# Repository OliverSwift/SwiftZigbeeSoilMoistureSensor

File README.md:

# Swift Zigbee Soil Moisture Sensor

This hardware project is about creating a Zigbee adapter to the existing Capacitive Soil Moisture Sensor 1.2 widely available.

## How to use it

[Here is](doc/Swift%20Zigbee%20Soil%20Moisture%20Sensor.pdf) the small user manual.

It works well with Conbee2 and SONOFF zigbee concentrators used with Home Assistant.

CR2032 coin battery should allow approximately two years of autonomy.

## Technical background

After some trials on STM32WB55 which permanently failed to connect to a zigbee concentrator (Conbee2) I finally chose the nrf52840 SOC from Nordic Semicondudtors. It is very well known in the BLE world and decided to test its Zigbee capabilities and it was successful. Best solutions are provided by Texas Instrument (CC2350) and Silabs (EFR32MG1) at the moment. Using nrf52840 for Zigbee is the challenge here.

The solution is based on ZephyrOS and NRF Connect SDK version 2.6.1 that includes ZBoss proprietary Zigbee stack. One of the challenging aspect of this project is the power consumption. The nrf52840 is able to enter deep sleep and only consumes 2.5µA approximately. Now I had to face that the Capacitive Sensor is based on a NE555. Surprisingly it is not the CMOS version and is supposed to be power supplied between 5 and 15V. But it can be with only 3.3V. Any attempt to power supply below this value resulted in unstable sensor. So I decided to use 3.3V for the whole device (MCU+sensor). This led to choosing a boost converter so a coin battery can be used, ideally CR2032.

The average current measurement is about 10µA, which should allow 2 year autonomy. Probe measurement is done every 30 minutes. When it occurs, the tiny LED lits.

The project was developed thanks to [nRF52840 DK board](doc/nRF52840_DK_User_Guide_v1.2.pdf). I used the OB JLink capability to flash the target board.

The nRF52840 module (E73-2G4M08S1C) comes from EBYTE. It doesn't have the external 32kHz crystal, but this one isn't useful for Zigbee applications.

Documentation folder includes:

- [Electronic schematics](doc/schematics-2.0.pdf)
- Main components datasheet (nrf52840 and tps61097a)
- [How to build and flash](doc/how_to_compile.md)

CAD folder includes:

- [KiCAD](cad/KiCAD) project files
- [FreeCAD](cad/FreeCAD) projet, a desparate attempt to design a [box with a lid](cad/FreeCAD/box+lid.stl).

## Project details

### Building system

The ZephyrOS ecosystem provides high level build system called _west_. It's a pile of Python scripts that doesn't do much else than invoking _cmake_. I quickly realized that cmake can be used solely without the cumbersome _west_ layer. I ended up with a simple Makefile to achieve the bare necessities. 

Forgot to say that I use Linux (Ubuntu or Debian), but this should work well with MacOSX either. I struggled to make Nordic tools to run on Ubuntu 24.04 (app images need to run without sandbox), but this is definitely possible.

Before compiling, ensure to run shell that sets environment variables properly. This tiny shell can be generated by SDK Management Tool.

Building for target is building for production. Use make _clean_, _prod_ and _flash_prod_ for final hardware.

Building for developement on DK is done with a simple 'make' and 'make flash'. In this configuration, serial line is used for message printing and measurement is performed every minute (see _prj.conf_ file).

### Zigbee part

Since it's a soil moisture sensor the device exposes a standard profile from ZHA. I added the battery profile to monitor the coin battery health. These two profiles are installed in main.c file. I crafted a derived battery profile structure myself (ZB_ZCL_DECLARE_POWER_CONFIG_ATTRIB_LIST2), because the predefined ones were either thick or missing additional definitions. Some missing stuff in ZBoss library. Since these structures are built with macros, it wasn't hard to build a more suitable one.

The device is a **Sleepy End Device** (SED), so it doesn't contribute to Zigbee network activities, it just reports periodically attributes.
Low power management was actually easy to do, the nrf52840 is very convenient for this. Choose the SDK wisely, the one that actually worked well for low power is SDK 2.6.1. Older ones resulted in 700µA consumption while asleep. This was way too far from promising 2µA or so. With SDK 2.6.1 the module only consumes 2.3µA when entering deep sleep.

Setting up a SED consists in calling '_zigbee_configure_sleepy_behavior(true)_' and '_power_down_unused_ram()_' at start up. The project configuration file (prj_power_saving.conf) contains:
- CONFIG_ZIGBEE_ROLE_END_DEVICE=y
- CONFIG_RAM_POWER_DOWN_LIBRARY=y

directives for that purpose.

The most tricky part of the code lies in Zigbee event management especially when joining or leaving a network. It also deals with factory reset.

Long poll interval is adjusted to 2 minutes instead of default 7 seconds. This drastically reduces average consumption. More than 2 minutes resulted in rejoin procedure failure or reparenting failure in the mesh. That caused headaches. My opinion is that this part is the weak one of ZBoss stack (also used with ESP32 systems). That's where Silabs and Texas Instrument are still leading the Zigbee field.

### I/O

Two analog inputs are setup, one for probe and one to measure battery voltage. Due to E73 module pinout, peculiar pins were chosen so they are accessible among the castellated ones.

The probe uses 10mA to make a humidity measurement. So it is driven by a MOSFET controlled by a GPIO. The probe is therefore powered when used. A serie of measurements are done in a loop until stable.

A led is useful with embedded devices. The one on this board reflects pairing process status and measurement operation.

As mentioned, the 32kHz external crystal is not used, saving some components. It is not needed for Zigbee because clock precision isn't required here. But, it is necessary to add the two following defines in project file:
- CONFIG_CLOCK_CONTROL_NRF_K32SRC_RC=y
- CONFIG_CLOCK_CONTROL_NRF_K32SRC_XTAL=n

This tells bootloader not to use internal 32kHz clock and not to calibrate it. Otherwise MCU won't boot stuck in calibration loop.

Using the internal 32kHz clock didn't result in extra consumption.

### Hardware part

As mentionned earlier, the external probe needs at least 3.3V. The nrf52840 usually runs at 3V (usual coin battery voltage), but supports up to 3.7V. I had to find a boost IC with low quiescent current so I can use a 3V battery and power supplies the external probe. Best choice so far is a TPS 61097a from Texas Instrument (TPS 61121 worked well either, but was twice as much more expensive).

### Measurement

The measurement operation occurs every 30 minutes. This is configured in _Kconfig_ file. An hour should suffice actually and save more power.

A low filter is applied on subsequent measures. It might be too strong and should be reduced.

Illustration of using _Swift Soil Moisture Sensor_ in Home Assistant:

## LICENSE

SPDX-License-Identifier: AGPL-3.0-or-later

[GNU AFFERO GENERAL PUBLIC LICENSE, Version 3, 19 November 2007](LICENSE)

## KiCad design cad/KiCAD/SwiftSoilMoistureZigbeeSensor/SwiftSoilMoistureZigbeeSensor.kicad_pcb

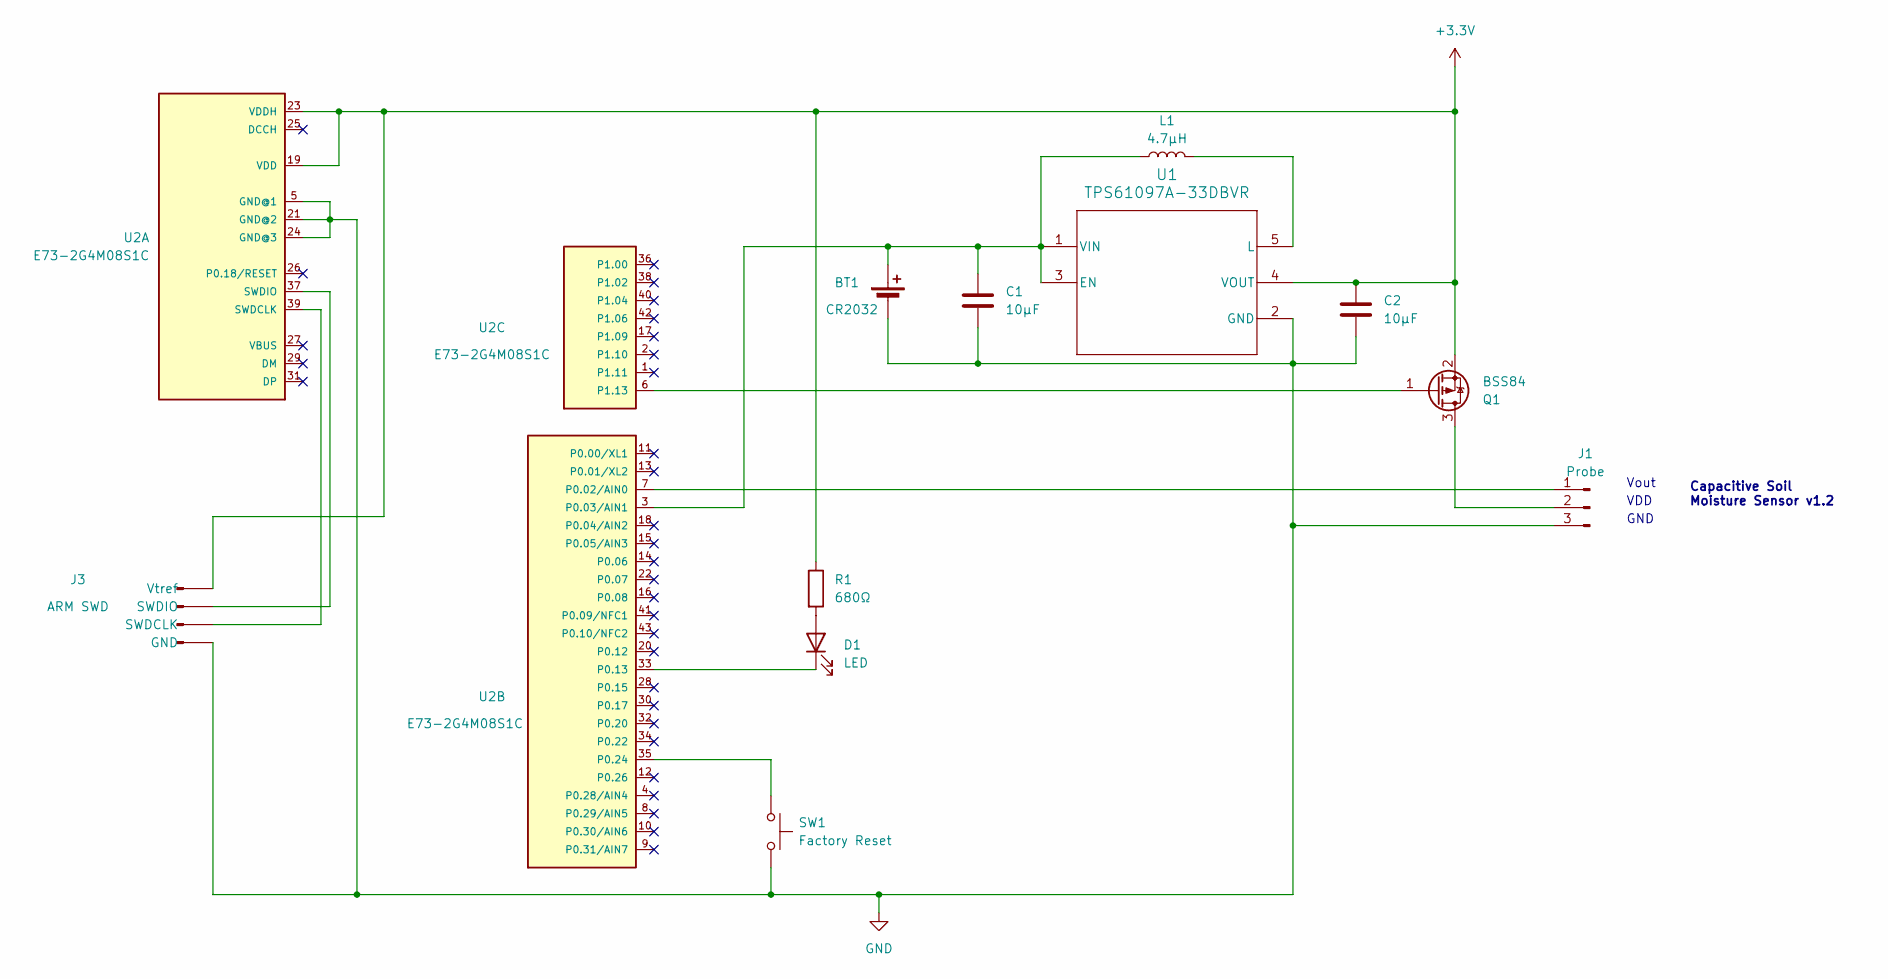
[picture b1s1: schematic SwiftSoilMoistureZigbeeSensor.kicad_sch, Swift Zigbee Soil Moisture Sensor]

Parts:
BT1: CR2032; BatteryHolder_Keystone_1060_1x2032; LCSC C22363833
C1, C2: 10µF; C_0603_1608Metric; LCSC C329937
D1: LED; LED_0603_1608Metric; LCSC C5246833
J1: Probe; PinHeader_1x03_P2.54mm_Horizontal; LCSC Male C2935928 / Female C7089182
J3: ARM SWD; PinHeader_1x04_P2.54mm_Vertical; LCSC C6332197
L1: 4.7µH; L_Taiyo-Yuden_NR-30xx; LCSC C87172
Q1: BSS84; SOT-23; LCSC C493579
R1: 680Ω; R_0603_1608Metric; LCSC C445820
SW1: Factory Reset; SW_SPST_B3S-1000; LCSC C231324
U1: TPS61097A-33DBVR; SOT-23-5_HandSoldering
U2: E73-2G4M08S1C; LCSC C356849

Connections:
+3.3V: C2.1, J3.1 (Vtref), Q1.2 (S), R1.1, U1.4 (VOUT), U2.19 (VDD), U2.23 (VDDH)
GND: BT1.2 (-), C1.2, C2.2, J1.3, J3.4 (GND), SW1.2, U1.2 (GND), U2.5 (GND@1), U2.21 (GND@2), U2.24 (GND@3)
unnamed: BT1.1 (+), C1.1, L1.1, U1.1 (VIN), U1.3 (EN), U2.3 (P0.03/AIN1)
unnamed: D1.2 (A), R1.2
unnamed: D1.1 (K), U2.33 (P0.13)
unnamed: J1.1, U2.7 (P0.02/AIN0)
unnamed: J1.2, Q1.3 (D)
unnamed: J3.3 (SWDCLK), U2.39 (SWDCLK)
unnamed: J3.2 (SWDIO), U2.37 (SWDIO)
unnamed: Q1.1 (G), U2.6 (P1.13)
unnamed: L1.2, U1.5 (L)
unnamed: SW1.1, U2.35 (P0.24)

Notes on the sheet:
GND
Vout
Capacitive Soil Moisture Sensor v1.2
VDD

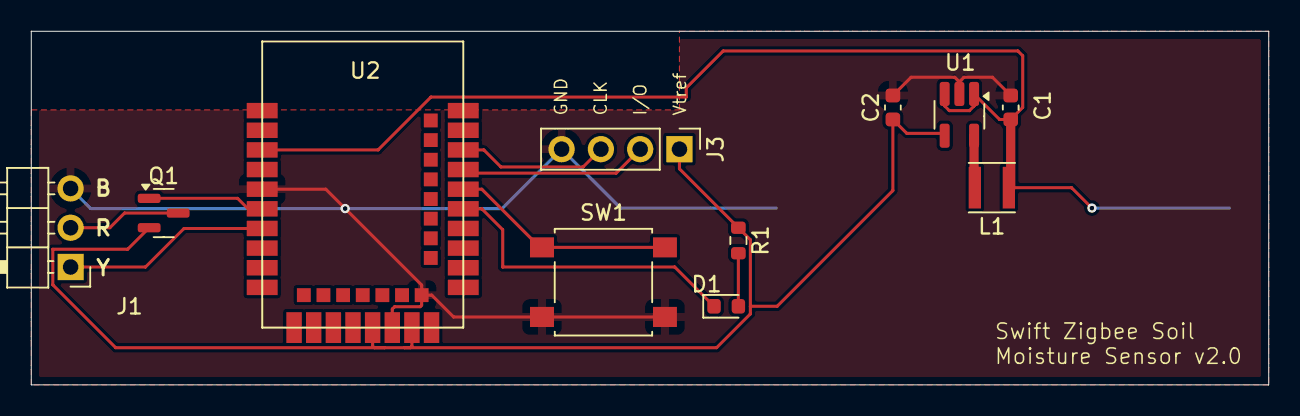
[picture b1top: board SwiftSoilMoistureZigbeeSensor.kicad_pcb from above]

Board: 2 copper layers, 80.0 x 22.9 mm, 12 parts (1 on the bottom side), 12 nets.

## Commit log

2023-08-04 First Zigbee Switch with nrf52840 dongle
2023-08-05 Reasssigned LEDs
2023-08-06 Integrated ADC code to read Analog AIN0 (pin P0.02)
2023-08-06 Signed reading from ADC in mV
2023-08-06 Clearing file names in this build
2023-08-17 Renamed files and symbols relative to Range Extender
2023-08-18 Now has Humidity Measurement cluster with reportable value attribute
2023-08-23 Replaced build.sh by a standard Makefile
2023-08-23 Made zip pkg name variable
2023-08-23 Using ZB app scheduler API for periodic measurement
2023-08-23 1 minute min report intervale. Bug with last value
2023-08-23 Much better way to change reporting info parameter
2023-08-25 Suppressed error when PKG is missing when cleaning
2023-08-25 Removed external LFXO 32768Hz XTAL. Use internal RC clock
2023-08-25 Cosmetics DTS cleanup
2023-08-25 Probe internal define, set to 1 minute. Low filter on subsequent measurements
2023-08-25 Changed variable range (bug)
2023-08-25 Power the probe though PIN1.15
2023-08-25 Can't drive probe with GPIO, need a MOSFET
2023-08-26 Cleaner probe actions
    Reactivated P1.15 probe command.
    Check after minimum voltage and warn if needed
    60 secs periodic probe measurement.
2023-08-26 Modules documentations
2023-08-28 SED should work. To be measured
2023-08-28 Cosmetic comment
2023-09-03 Changed low filter and rounding value
2023-09-03 More doc
2023-09-08 Use zephyr logging
2023-09-08 Low filter on ADC values
2023-09-09 Formatting issue
2023-09-16 Added power saving config
2023-09-17 Make led blink until joined
2023-09-17 Driving P-MOS so active pin is Low
2023-09-22 Moved to nrf52840dk
2023-09-22 DK schematics added to doc
2023-09-22 Dongle files and Makefile targets cleanup
2023-10-08 Really remove logs and serial
2023-10-09 DK documentation
2023-10-15 Moved led set after state computation update. Minor
2023-10-15 Sleepy settings for prj
2023-10-15 Only start measurement when ZB join is successful
2023-10-15 Removed dongle specific stuff
2023-10-15 Clean up again in Makefile
2023-10-15 Shortened probe power supply time
2023-10-15 SED target in Makefile
2023-10-15 Validated SED target
2023-10-15 Cleanup
2023-10-15 Removed USB CDC ACM stuff
2023-10-15 Removed conflicting conf in SED build
2023-10-25 Constants definition
2023-10-28 Added battery voltage measurement and ZB Power Config Cluster
2023-10-28 Test battery voltage measurement
2023-10-29 Code cleanup. Separate battery function
2023-11-11 Wrong attribute value for battery
2023-11-11 Adjusted Power Config cluster creation
2023-11-11 Cleaned up battery structure. Now reporting battery percentage
2023-11-11 Percentage is actually half integer
2023-11-18 Changed reporting intervals. Cleaner code.
2023-11-24 Better filtering. 4H min report time. Report battery percentage if needed.
2023-12-10 Use P1.13 instead of P1.15. Because of E37 pinout
2023-12-29 Compile how to doc
2024-01-10 nrf52840 product spec update
2024-02-09 Better doc for SDK and Flashing tool install
2024-06-30 typo doc
2024-07-03 Removed default factory button management. Fixed poll_interval bug
2024-07-03 Changed Factory Reset button to BTN2
2024-07-03 Boost 3V TI doc
2024-07-03 Change Boost to TPS61221
2024-07-03 Display message when compiling with 3V calibration
2024-07-04 Start of CAD work
2024-07-04 Added E73-2G4M08S1C footprint
2024-07-04 Ignore KiCAD fp cache file
2024-07-04 Footprint associations
2024-07-07 Replaces BTN2 with BTN3
2024-07-07 Routing
2024-07-08 Better how to compile doc
2024-07-08 CAD Stuff
2024-07-08 Prints
2024-07-08 LED and R1 sizes to 0603
2024-07-08 Comp Label renaming
2024-07-10 Reddundant code
2024-07-10 Calling power_down_unued_ram for sed version
2024-07-10 Custome Kconfig
2024-07-11 32KHz source configuration
2024-07-11 Remove comment
2024-07-11 Ground planes
2024-07-11 Relative project paths in Kicad files
2024-07-16 JLCPCB Kicad Fab settings
2024-07-16 Ignore Kicad fab files
2024-07-23 Imported 3D model of the E73 module
2024-07-27 Added LCSC refs
2024-07-28 Mark unconnected pins. Enlarged L1 connections
2024-07-28 Schematics of this project
2024-08-12 Changed SWD connector
2024-08-12 Rewworked SWD connector
2024-08-13 Bad LED wiring
2024-08-13 New schematics
2024-08-13 1 sec probe power instead of 500ms
2024-08-13 Reverted LED state because of HW error
2024-08-16 Force battery report as needed
2024-08-17 Made 32K CLOCK based on RC
2024-08-17 Better after join startup code
2024-08-17 Boards defs are useless
2024-08-18 Preserve probe power supply until value is ok
2024-08-18 Removed useless config def
2024-08-18 Keep build log and md5 of generated hex
2024-08-19 Removed main low pass filter. Removed force_report arg for battery measurement
2024-08-22 Ignore archives dir
2024-08-22 LED wiring for final hadrware
2024-08-23 Set BOARD and CONF_FILE in CMakeLists.txt
2024-08-23 Reworked entry Makefile
2024-08-24 Suppressed turbo_poll that prevents many Data Request frames
2024-08-25 Added CONFIG stuff to avoid cmake warnings
2024-08-26 Low filter battery voltage measures
2024-08-26 PCB Version 1.1
2024-08-26 Updated LCSC BOM
2024-08-27 Change LCSC part ref
2024-08-27 More files to ignore
2024-08-27 Low filter computation round error
2024-08-27 Prod target based on cmake and nrfjprog
2024-08-28 Voltage low filter computation issue. Factory reset code moved.
2024-08-31 Reworkd start up code. Set Long Poll to reasonable duration
2024-09-01 Added -j to cmake build
2024-09-02 Changed cmake parallel option
2024-09-10 680ohm is enough. SWD silk text for convinience
2024-09-16 Rewrote factory reset part
2024-09-17 Inductance footprint modified. Probe print
2024-09-17 Delay attribute report on first start
2024-09-17 Prod dependancy
2024-09-19 Added 3D models for L1 and SW1
2024-09-22 Colored button
2024-09-22 Better coil model
2024-09-23 Schematics version update.
2024-09-23 Send attributes ASAP and 15 sec after startup
2024-09-23 Added readback protection action
2024-09-23 Nice 3D illustration image
2024-09-23 Add README.md
2024-09-24 Force attribute update on second call at startup
2024-10-01 Replaced Jumper with SB
2024-10-01 New hardware illustration
2024-10-03 Invisible SWD header. New hardware illustration image
2024-10-03 User manual
2024-10-04 Probe measurement improvement
2024-10-05 Removed Jumper/SB
2024-10-05 Doc updated
2024-10-08 Arranged cad stuff
2024-10-08 3D box cad
2024-10-08 New schematics document
2024-10-08 User manual updated
2024-10-08 Updated BOX
2024-10-08 Minor cosmetics changes
2024-10-12 Doc and copyright statements
2024-10-13 Changed TPS61221 to TPS61097
2024-10-13 BOM update
2024-10-17 Separate AP protect procedure
2024-10-24 Doc update
2024-10-26 Enlarged box
2024-11-03 Project logo
2024-11-03 Modified box. Slightly enlarged
2024-11-03 Validated new HW with new boost
2024-11-04 Updated user manual
2024-11-26 Capacitive Soild Moisture Sensor image
2024-11-28 Improved illustration image
2024-12-06 Illustration image correction. Again
2024-12-07 HA screenshot
2024-12-11 Add LICENSE
2024-12-12 AGPL v3
2024-12-12 Typo
2024-12-16 Grammar. Box and Lid CAD
2024-12-19 Grammar
2024-12-22 Recentered lid hole
2025-01-15 Cad Clean up
2025-02-10 Modified lid in STL
